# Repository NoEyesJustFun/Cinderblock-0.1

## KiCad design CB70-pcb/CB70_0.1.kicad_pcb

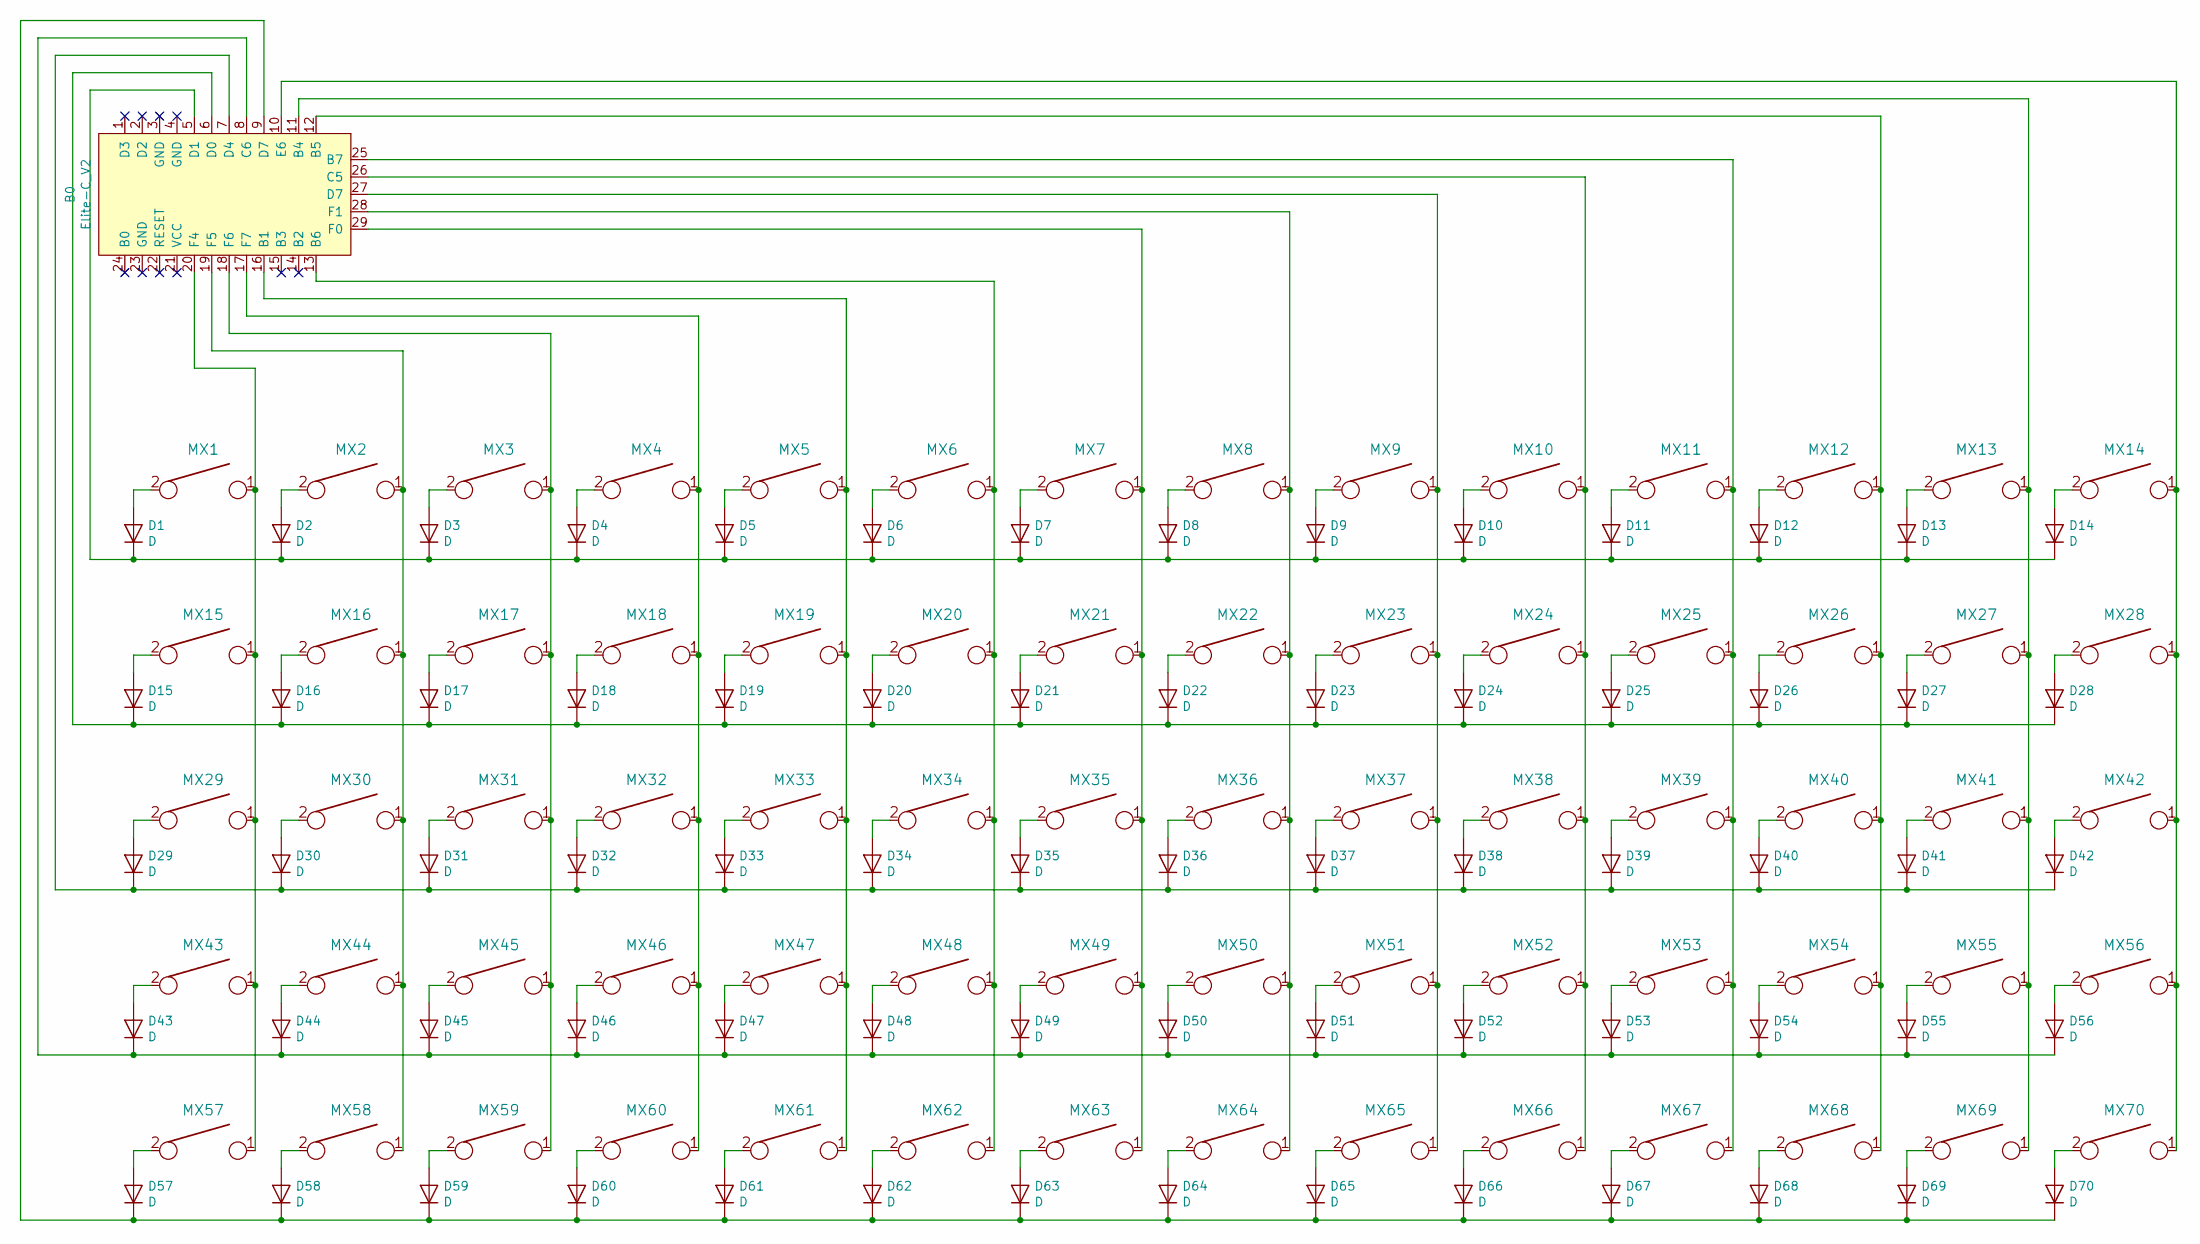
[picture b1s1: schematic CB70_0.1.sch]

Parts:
B0: Elite-C_V2; Elite-C
D1, D2, D3, D4, D5, D6, D7, D8, D9, D10, D11, D12, D13, D14, D15, D16, D17, D18, D19, D20, D21, D22, D23, D24, D25, D26, D27, D28, D29, D30, D31, D32, D33, D34, D35, D36, D37, D38, D39, D40, D41, D42, D43, D44, D45, D46, D47, D48, D49, D50, D51, D52, D53, D54, D55, D56, D57, D58, D59, D60, D61, D62, D63, D64, D65, D66, D67, D68, D69, D70: D; Diode
MX1, MX2, MX3, MX4, MX5, MX6, MX7, MX8, MX9, MX10, MX11, MX12, MX13, MX14, MX15, MX16, MX17, MX18, MX19, MX20, MX21, MX22, MX23, MX24, MX25, MX26, MX27, MX28, MX29, MX30, MX31, MX32, MX33, MX34, MX35, MX36, MX37, MX38, MX39, MX40, MX41, MX42, MX43, MX44, MX45, MX46, MX47, MX48, MX49, MX50, MX51, MX52, MX53, MX54, MX55, MX56, MX57, MX58, MX59, MX60, MX61, MX62, MX63, MX64, MX65, MX66, MX67, MX68, MX69, MX70: KEYSW; SW_MX

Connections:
unnamed: B0.5 (D1), D1.1 (K), D2.1 (K), D3.1 (K), D4.1 (K), D5.1 (K), D6.1 (K), D7.1 (K), D8.1 (K), D9.1 (K), D10.1 (K), D11.1 (K), D12.1 (K), D13.1 (K), D14.1 (K)
unnamed: B0.6 (D0), D15.1 (K), D16.1 (K), D17.1 (K), D18.1 (K), D19.1 (K), D20.1 (K), D21.1 (K), D22.1 (K), D23.1 (K), D24.1 (K), D25.1 (K), D26.1 (K), D27.1 (K), D28.1 (K)
unnamed: B0.7 (D4), D29.1 (K), D30.1 (K), D31.1 (K), D32.1 (K), D33.1 (K), D34.1 (K), D35.1 (K), D36.1 (K), D37.1 (K), D38.1 (K), D39.1 (K), D40.1 (K), D41.1 (K), D42.1 (K)
unnamed: B0.8 (C6), D43.1 (K), D44.1 (K), D45.1 (K), D46.1 (K), D47.1 (K), D48.1 (K), D49.1 (K), D50.1 (K), D51.1 (K), D52.1 (K), D53.1 (K), D54.1 (K), D55.1 (K), D56.1 (K)
unnamed: B0.9 (D7), D57.1 (K), D58.1 (K), D59.1 (K), D60.1 (K), D61.1 (K), D62.1 (K), D63.1 (K), D64.1 (K), D65.1 (K), D66.1 (K), D67.1 (K), D68.1 (K), D69.1 (K), D70.1 (K)
unnamed: B0.10 (E6), MX14.1, MX28.1, MX42.1, MX56.1, MX70.1
unnamed 10: B0.11 (B4), MX13.1, MX27.1, MX41.1, MX55.1, MX69.1; also elsewhere on the board
unnamed: B0.12 (B5), MX12.1, MX26.1, MX40.1, MX54.1, MX68.1
unnamed 12: B0.13 (B6), MX6.1, MX20.1, MX34.1, MX48.1, MX62.1; also elsewhere on the board
unnamed: B0.16 (B1), MX5.1, MX19.1, MX33.1, MX47.1, MX61.1
unnamed: B0.17 (F7), MX4.1, MX18.1, MX32.1, MX46.1, MX60.1
unnamed: B0.18 (F6), MX3.1, MX17.1, MX31.1, MX45.1, MX59.1
unnamed: B0.19 (F5), MX2.1, MX16.1, MX30.1, MX44.1, MX58.1
unnamed 19: B0.20 (F4), MX1.1, MX15.1, MX29.1, MX43.1, MX57.1; also elsewhere on the board
unnamed: B0.25 (B7), MX11.1, MX25.1, MX39.1, MX53.1, MX67.1
unnamed: B0.26 (C5), MX10.1, MX24.1, MX38.1, MX52.1, MX66.1
unnamed: B0.27 (D7), MX9.1, MX23.1, MX37.1, MX51.1, MX65.1
unnamed 27: B0.28 (F1), MX8.1, MX22.1, MX36.1, MX50.1, MX64.1; also elsewhere on the board
unnamed: B0.29 (F0), MX7.1, MX21.1, MX35.1, MX49.1, MX63.1
unnamed: D1.2 (A), MX1.2
unnamed: D2.2 (A), MX2.2
unnamed: D3.2 (A), MX3.2
unnamed: D4.2 (A), MX4.2
unnamed: D5.2 (A), MX5.2
unnamed: D6.2 (A), MX6.2
unnamed: D7.2 (A), MX7.2
unnamed: D8.2 (A), MX8.2
unnamed: D9.2 (A), MX9.2
unnamed: D10.2 (A), MX10.2
unnamed: D11.2 (A), MX11.2
unnamed: D12.2 (A), MX12.2
unnamed: D13.2 (A), MX13.2
unnamed: D14.2 (A), MX14.2
unnamed: D15.2 (A), MX15.2
unnamed: D16.2 (A), MX16.2
unnamed: D17.2 (A), MX17.2
unnamed: D18.2 (A), MX18.2
unnamed: D19.2 (A), MX19.2
unnamed: D20.2 (A), MX20.2
unnamed: D21.2 (A), MX21.2
unnamed: D22.2 (A), MX22.2
unnamed: D23.2 (A), MX23.2
unnamed: D24.2 (A), MX24.2
unnamed: D25.2 (A), MX25.2
unnamed: D26.2 (A), MX26.2
unnamed: D27.2 (A), MX27.2
unnamed: D28.2 (A), MX28.2
unnamed: D29.2 (A), MX29.2
unnamed: D30.2 (A), MX30.2
unnamed: D31.2 (A), MX31.2
unnamed: D32.2 (A), MX32.2
unnamed: D33.2 (A), MX33.2
unnamed: D34.2 (A), MX34.2
unnamed: D35.2 (A), MX35.2
unnamed: D36.2 (A), MX36.2
unnamed: D37.2 (A), MX37.2
unnamed: D38.2 (A), MX38.2
unnamed: D39.2 (A), MX39.2
unnamed: D40.2 (A), MX40.2
unnamed 69: D41.2 (A), MX41.2; also elsewhere on the board
unnamed: D42.2 (A), MX42.2
unnamed 71: D43.2 (A), MX43.2; also elsewhere on the board
unnamed: D44.2 (A), MX44.2
unnamed: D45.2 (A), MX45.2
unnamed: D46.2 (A), MX46.2
unnamed: D47.2 (A), MX47.2
unnamed: D48.2 (A), MX48.2
unnamed: D49.2 (A), MX49.2
unnamed: D50.2 (A), MX50.2
unnamed: D51.2 (A), MX51.2
unnamed: D52.2 (A), MX52.2
unnamed: D53.2 (A), MX53.2
unnamed: D54.2 (A), MX54.2
unnamed: D55.2 (A), MX55.2
unnamed: D56.2 (A), MX56.2
unnamed: D57.2 (A), MX57.2
unnamed: D58.2 (A), MX58.2
unnamed: D59.2 (A), MX59.2
unnamed: D60.2 (A), MX60.2
unnamed: D61.2 (A), MX61.2
unnamed 90: D62.2 (A), MX62.2; also elsewhere on the board
unnamed: D63.2 (A), MX63.2
unnamed 92: D64.2 (A), MX64.2; also elsewhere on the board
unnamed: D65.2 (A), MX65.2
unnamed: D66.2 (A), MX66.2
unnamed: D67.2 (A), MX67.2
unnamed: D68.2 (A), MX68.2
unnamed: D69.2 (A), MX69.2
unnamed: D70.2 (A), MX70.2

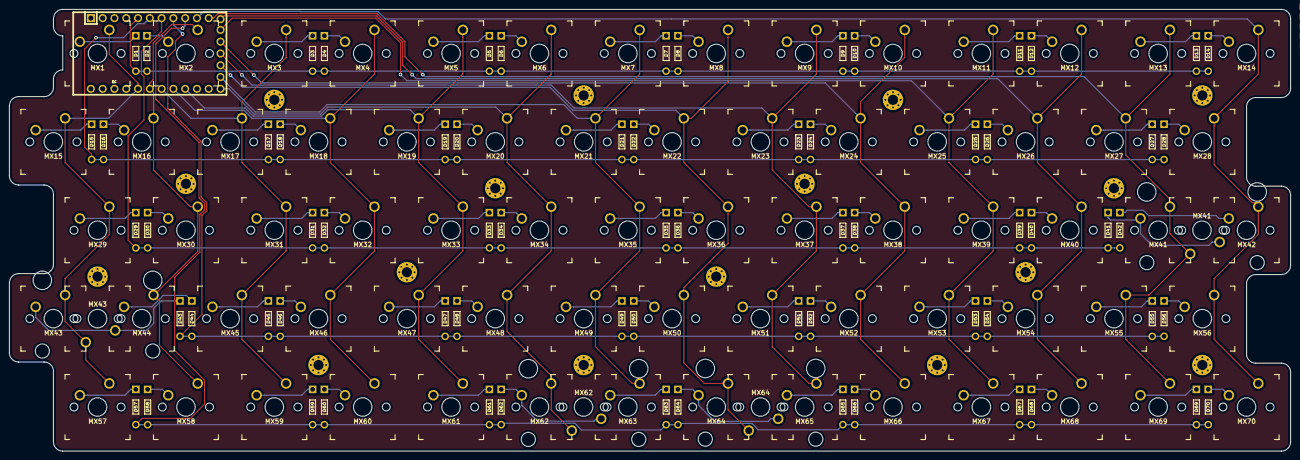
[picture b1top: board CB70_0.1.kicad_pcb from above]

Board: 2 copper layers, 276.1 x 95.2 mm, 145 parts (1 on the bottom side), 89 nets.

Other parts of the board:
MX41#2, MX43#2, MX62#2, MX64#2: KEYSW; SW_MX

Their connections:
unnamed 10: MX41#2.1; also elsewhere on the board
unnamed 12: MX62#2.1; also elsewhere on the board
unnamed 19: MX43#2.1; also elsewhere on the board
unnamed 27: MX64#2.1; also elsewhere on the board
unnamed 69: MX41#2.2; also elsewhere on the board
unnamed 71: MX43#2.2; also elsewhere on the board
unnamed 90: MX62#2.2; also elsewhere on the board
unnamed 92: MX64#2.2; also elsewhere on the board

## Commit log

2020-03-07 Files Update
